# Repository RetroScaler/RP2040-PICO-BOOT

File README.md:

# RP2040-PICO-BOOT
The RP2040 PICO BOOT allows you to build your own IPL replacement modchip，It is a modified version of the Raspberry Pi Pico.

## Features

- Includes all the functions of Raspberry Pi Pico
- Without any driver, you can burn the program through Type-C cable
- Add a 'Reset' button

## Pictures

3D Picture of PCBA

The pinout 

## 🤝 Support

Contributions, issues, and feature requests are welcome!

if you like this project, stay tuned !

You can quickly purchase the finished product with this link：[Go to AliExpress shopping platform](https://www.aliexpress.us/item/3256804731684211.html?spm=a2g0o.store_pc_allProduct.8148356.3.6d2d4653RMWMQH&pdp_npi=2%40dis%21USD%21US%20%244.60%21US%20%243.27%21%21%21%21%21%40211b88f116768734920522999e0baf%2112000031082566413%21sh&gatewayAdapt=glo2usa&_randl_shipto=US)

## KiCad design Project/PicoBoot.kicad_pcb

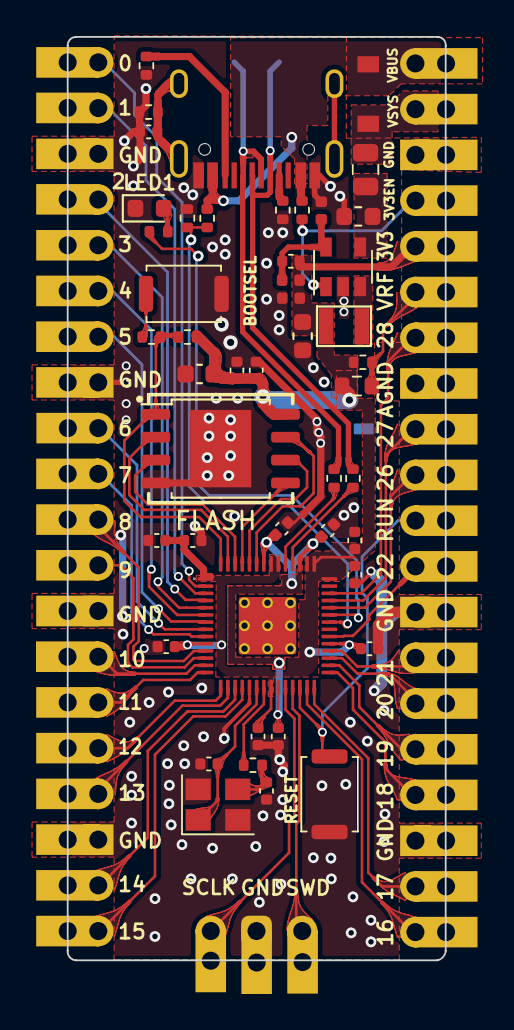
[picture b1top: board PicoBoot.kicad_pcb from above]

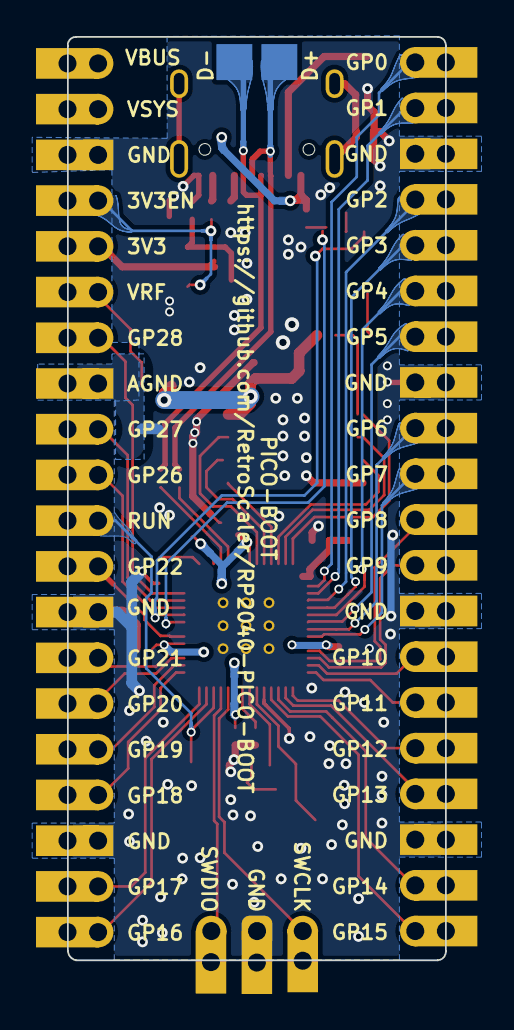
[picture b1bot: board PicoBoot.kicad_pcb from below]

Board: 2 copper layers, 21.0 x 51.3 mm, 53 parts (5 on the bottom side), 60 nets.

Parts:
C1, C9, C17: 10uf; C_0603_1608Metric
C2, C19: 22pf; C_0402_1005Metric
C3, C10: 1uf; C_0402_1005Metric
C4: 22pF; C_0402_1005Metric
C5, C6, C7, C8, C11, C12, C13, C14, C15, C16, C18: 100nf; C_0402_1005Metric
C101: 0.1uf; C_0402_1005Metric
D1: 1N4002W; D_SOD-123
F1: 0805L050WR; Fuse_0805_2012Metric
FLASH: W25Q16JVUXIQ; SOIC-8_5.23x5.23mm_P1.27mm
GPIO25_RESISTOR1: 470; R_0402_1005Metric
J2: TSA343G00-250J2; SW_Push_SPST_NO_Alps_SKRK
J3, J4: 2.54mm header 01x20; PinHeader_1x20_P2.54mm_Vertical
J5: Conn_01x03_Male; PinHeader_1x03_P2.54mm_Vertical
L1: 2.2uH; WPN252010UF2R2MT
LED1: LED_0603; LED_0603_1608Metric
NT1: NetTie_2; NetTie-2_SMD_Pad0.5mm
R1, R11: 1K; R_0402_1005Metric
R2, R103: 10K; R_0402_1005Metric
R3, R4: 27r; R_0402_1005Metric
R5, R6: 5.1K; R_0402_1005Metric
R7: 100K; R_0402_1005Metric
R8: 680K; R_0402_1005Metric
R9: 200; R_0603_1608Metric
R10: 1; R_0402_1005Metric
R12: 150K; R_0402_1005Metric
R101: 5.6K; R_0402_1005Metric
R102: 220; R_0402_1005Metric
RSW1: TSA343G00-250J2; SW_Push_SPST_NO_Alps_SKRK
TP1, TP2: TestPoint; CustomTestPoint
U1: TD6810-ADJ; SOT-23-5
U3: RP2040; RP2040-QFN-56
USB1: TYPE-C-31-M-12; HRO-TYPE-C-31-M-12
Y1: 3225_4P; Crystal_SMD_3225-4Pin_3.2x2.5mm

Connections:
3V3_EN: J4.4, R7.1, U1.1 (RUN)
+1V1: C3.1, C6.1, C7.1, U3.23 (DVDD), U3.45 (VREG_VOUT), U3.50 (DVDD)
+3V3: C4.2, C5.1, C8.1, C9.1, C10.1, C11.1, C12.1, C13.1, C14.1, C15.1, C16.1, C17.1, C18.1, FLASH.8 (VCC), J4.5, L1.2, R2.1, R8.1, R9.1, R10.2, U3.1 (IOVDD), U3.10 (IOVDD), U3.22 (IOVDD), U3.33 (IOVDD), U3.42 (IOVDD), U3.43 (ADC_AVDD), U3.44 (VREG_IN), U3.48 (USB_VDD), U3.49 (IOVDD)
/ADC_VREF: J4.6, R9.2, R10.1
/D+: R3.2, U3.47 (USB_DP)
/D-: R4.2, U3.46 (USB_DM)
/GPIO0: J3.20, U3.2 (GPIO0)
/GPIO1: J3.19, U3.3 (GPIO1)
/GPIO2: J3.17, U3.4 (GPIO2)
/GPIO3: J3.16, U3.5 (GPIO3)
/GPIO4: J3.15, U3.6 (GPIO4)
/GPIO5: J3.14, U3.7 (GPIO5)
/GPIO6: J3.12, U3.8 (GPIO6)
/GPIO7: J3.11, U3.9 (GPIO7)
/GPIO8: J3.10, U3.11 (GPIO8)
/GPIO9: J3.9, U3.12 (GPIO9)
/GPIO10: J3.7, U3.13 (GPIO10)
/GPIO11: J3.6, U3.14 (GPIO11)
/GPIO12: J3.5, U3.15 (GPIO12)
/GPIO13: J3.4, U3.16 (GPIO13)
/GPIO14: J3.2, U3.17 (GPIO14)
/GPIO15: J3.1, U3.18 (GPIO15)
/GPIO16: J4.20, U3.27 (GPIO16)
/GPIO17: J4.19, U3.28 (GPIO17)
/GPIO18: J4.17, U3.29 (GPIO18)
/GPIO19: J4.16, U3.30 (GPIO19)
/GPIO20: J4.15, U3.31 (GPIO20)
/GPIO21: J4.14, U3.32 (GPIO21)
/GPIO22: J4.12, U3.34 (GPIO22)
/GPIO24: R101.2, R103.1, U3.36 (GPIO24)
/GPIO25: GPIO25_RESISTOR1.2, U3.37 (GPIO25)
/GPIO26_ADC0: J4.10, U3.38 (GPIO26_ADC0)
/GPIO27_ADC1: J4.9, U3.39 (GPIO27_ADC1)
/GPIO28_ADC2: J4.7, U3.40 (GPIO28_ADC2)
/QSPI_SCLK: FLASH.6 (CLK), U3.52 (QSPI_SCLK)
/QSPI_SD0: FLASH.5 (DI(IO0)), U3.53 (QSPI_SD0)
/QSPI_SD1: FLASH.2 (DO(IO1)), U3.55 (QSPI_SD1)
/QSPI_SD2: FLASH.3 (IO2), U3.54 (QSPI_SD2)
/QSPI_SD3: FLASH.7 (IO3), U3.51 (QSPI_SD3)
/QSPI_SS: FLASH.1 (~CS), R1.1, R2.2, U3.56 (QSPI_SS)
/RUN: J4.11, RSW1.2, U3.26 (RUN)
/SWCLK: J5.1, U3.24 (SWCLK)
/SWD: J5.3, U3.25 (SWD)
/~USB_BOOT: J2.1, R1.2
AGND: J4.8, NT1.2
GND: C1.2, C2.1, C3.2, C5.2, C6.2, C7.2, C8.2, C9.2, C10.2, C11.2, C12.2, C13.2, C14.2, C15.2, C16.2, C17.2, C18.2, C19.1, C101.1, FLASH.4 (GND), J2.2, J3.3, J3.8, J3.13, J3.18, J4.3, J4.13, J4.18, J5.2, LED1.1 (K), NT1.1, R5.1, R6.1, R12.1, R102.2, R103.2, RSW1.1, U1.2 (GND), U3.19 (TESTEN), U3.57 (GND), USB1.1 (GND), USB1.12 (GND), Y1.2, Y1.4
unnamed: C1.1, F1.1, U1.4 (VIN)
unnamed: C4.1, R8.2, R12.2, U1.5 (FB)
unnamed: C19.2, R11.2, Y1.3
unnamed: C101.2, R102.1, USB1.13 (SHIELD)
unnamed: GPIO25_RESISTOR1.1, LED1.2 (A)
unnamed: L1.1, U1.3 (SW)
unnamed: R5.2, USB1.4 (CC1)
unnamed: R6.2, USB1.10 (CC2)
USB_D+: R3.1, TP1.1, USB1.6 (DP1), USB1.8 (DP2)
USB_D-: R4.1, TP2.1, USB1.5 (DN2), USB1.7 (DN1)
VBUS: D1.2 (A), J4.1, R7.2, R101.1, USB1.2 (VBUS), USB1.11 (VBUS)
VSYS: D1.1 (K), F1.2, J4.2
XIN: C2.2, U3.20 (XIN), Y1.1
XOUT: R11.1, U3.21 (XOUT)

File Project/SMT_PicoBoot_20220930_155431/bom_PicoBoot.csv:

Comment,Description,Designator,Footprint,LibRef,Pins,Quantity
"","",",,","","","",3
"10uf 0603","Capacitor SMD 0603 (1608 Metric), square (rectangular) end terminal, IPC_7351 nominal, (Body size source: http://www.tortai-tech.com/upload/download/20111020232333690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, generated with kicad-footprint-generator","C1,C9","C_0603_1608Metric","","",2
"22pf 0402","Capacitor SMD 0402 (1005 Metric), square (rectangular) end terminal, IPC_7351 nominal, (Body size source: IPC-SM-782 page 76, https://www.pcb-3d.com/wordpress/wp-content/uploads/ipc-sm-7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, generated with kicad-footprint-generator","C2,C19","C_0402_1005Metric","","",2
"1uf 0402","Capacitor SMD 0402 (1005 Metric), square (rectangular) end terminal, IPC_7351 nominal, (Body size source: IPC-SM-782 page 76, https://www.pcb-3d.com/wordpress/wp-content/uploads/ipc-sm-7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, generated with kicad-footprint-generator","C3,C10","C_0402_1005Metric","","",2
"22pF ","Capacitor SMD 0402 (1005 Metric), square (rectangular) end terminal, IPC_7351 nominal, (Body size source: IPC-SM-782 page 76, https://www.pcb-3d.com/wordpress/wp-content/uploads/ipc-sm-7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, generated with kicad-footprint-generator","C4","C_0402_1005Metric","","",1
"100nf 0402","Capacitor SMD 0402 (1005 Metric), square (rectangular) end terminal, IPC_7351 nominal, (Body size source: IPC-SM-782 page 76, https://www.pcb-3d.com/wordpress/wp-content/uploads/ipc-sm-7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, generated with kicad-footprint-generator","C6,C7,C11,C13,C14,C8,C5,C16,C18,C15,C12","C_0402_1005Metric","","",11
"10uf 0402","Capacitor SMD 0603 (1608 Metric), square (rectangular) end terminal, IPC_7351 nominal, (Body size source: IPC-SM-782 page 76, https://www.pcb-3d.com/wordpress/wp-content/uploads/ipc-sm-7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, generated with kicad-footprint-generator","C17","C_0603_1608Metric","","",1
"0.1uf 0402","Capacitor SMD 0402 (1005 Metric), square (rectangular) end terminal, IPC_7351 nominal, (Body size source: IPC-SM-782 page 76, https://www.pcb-3d.com/wordpress/wp-content/uploads/ipc-sm-7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, generated with kicad-footprint-generator","C101","C_0402_1005Metric","","",1
"1N4002W","SOD-123","D1","D_SOD-123","","",1
"0805L050WR","Fuse SMD 0805 (2012 Metric), square (rectangular) end terminal, IPC_7351 nominal, (Body size source: https://docs.google.com/spreadsheets/d/1BsfQQcO9C6DZCsRaXUlF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, generated with kicad-footprint-generator","F1","Fuse_0805_2012Metric","","",1
"W25Q16JVUXIQ","SOIC, 8 Pin (http://www.winbond.com/resource-files/w25q32jv%20revg%200327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, generated with kicad-footprint-generator ipc_gullwing_generator.py","FLASH","SOIC-8_5.23x5.23mm_P1.27mm","","",1
"LED_0402","LED SMD 0402 (1005 Metric), square (rectangular) end terminal, IPC_7351 nominal, (Body size source: http://www.tortai-tech.com/upload/download/20111020232333690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, generated with kicad-footprint-generator","GPIO25_LED1","LED_0402_1005Metric","","",1
"470 0402","Resistor SMD 0402 (1005 Metric), square (rectangular) end terminal, IPC_7351 nominal, (Body size source: IPC-SM-782 page 72, https://www.pcb-3d.com/wordpress/wp-content/uploads/ipc-sm-7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, generated with kicad-footprint-generator","GPIO25_RESISTOR1","R_0402_1005Metric","","",1
"MountingHole","Mounting Hole 2.1mm, no annular","H4,H3,H1,H2","MountingHole_2.1mm","","",4
"TSA343G00-250J2","http://www.alps.com/prod/info/E/HTML/Tact/SurfaceMount/SKRK/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","J2,RSW1","SW_Push_SPST_NO_Alps_SKRK","","",2
"2.54mm header 01x20","Through hole straight pin header, 1x20, 2.54mm pitch, single row","J4,J3","PinHeader_1x20_P2.54mm_Vertical","","",2
"Conn_01x03_Male","Through hole straight pin header, 1x03, 2.54mm pitch, single row","J5","PinHeader_1x03_P2.54mm_Vertical","","",1
"2.2uH","","L1","WPN252010UF2R2MT","","",1
"NetTie_2","Net tie, 2 pin, 0.5mm square SMD pads","NT1","NetTie-2_SMD_Pad0.5mm","","",1
"1K 0402","Resistor SMD 0402 (1005 Metric), square (rectangular) end terminal, IPC_7351 nominal, (Body size source: IPC-SM-782 page 72, https://www.pcb-3d.com/wordpress/wp-content/uploads/ipc-sm-7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, generated with kicad-footprint-generator","R1,R11","R_0402_1005Metric","","",2
"10K 0402","Resistor SMD 0402 (1005 Metric), square (rectangular) end terminal, IPC_7351 nominal, (Body size source: IPC-SM-782 page 72, https://www.pcb-3d.com/wordpress/wp-content/uploads/ipc-sm-7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, generated with kicad-footprint-generator","R2,R103","R_0402_1005Metric","","",2
"27r 0402 resistor","Resistor SMD 0402 (1005 Metric), square (rectangular) end terminal, IPC_7351 nominal, (Body size source: IPC-SM-782 page 72, https://www.pcb-3d.com/wordpress/wp-content/uploads/ipc-sm-7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, generated with kicad-footprint-generator","R4,R3","R_0402_1005Metric","","",2
"5.1K 0402","Resistor SMD 0402 (1005 Metric), square (rectangular) end terminal, IPC_7351 nominal, (Body size source: IPC-SM-782 page 72, https://www.pcb-3d.com/wordpress/wp-content/uploads/ipc-sm-7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, generated with kicad-footprint-generator","R5,R6","R_0402_1005Metric","","",2
"100K 0402","Resistor SMD 0402 (1005 Metric), square (rectangular) end terminal, IPC_7351 nominal, (Body size source: IPC-SM-782 page 72, https://www.pcb-3d.com/wordpress/wp-content/uploads/ipc-sm-7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, generated with kicad-footprint-generator","R7","R_0402_1005Metric","","",1
"680K","Resistor SMD 0402 (1005 Metric), square (rectangular) end terminal, IPC_7351 nominal, (Body size source: http://www.tortai-tech.com/upload/download/20111020232333690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, generated with kicad-footprint-generator","R8","R_0402_1005Metric","","",1
"200 0603","Resistor SMD 0603 (1608 Metric), square (rectangular) end terminal, IPC_7351 nominal, (Body size source: IPC-SM-782 page 72, https://www.pcb-3d.com/wordpress/wp-content/uploads/ipc-sm-7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, generated with kicad-footprint-generator","R9","R_0603_1608Metric","","",1
"1 0402","Resistor SMD 0402 (1005 Metric), square (rectangular) end terminal, IPC_7351 nominal, (Body size source: IPC-SM-782 page 72, https://www.pcb-3d.com/wordpress/wp-content/uploads/ipc-sm-7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, generated with kicad-footprint-generator","R10","R_0402_1005Metric","","",1
"150K","Resistor SMD 0402 (1005 Metric), square (rectangular) end terminal, IPC_7351 nominal, (Body size source: http://www.tortai-tech.com/upload/download/20111020232333690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, generated with kicad-footprint-generator","R12","R_0402_1005Metric","","",1
"5.6K 0402","Resistor SMD 0402 (1005 Metric), square (rectangular) end terminal, IPC_7351 nominal, (Body size source: IPC-SM-782 page 72, https://www.pcb-3d.com/wordpress/wp-content/uploads/ipc-sm-7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, generated with kicad-footprint-generator","R101","R_0402_1005Metric","","",1
"220 0402","Resistor SMD 0402 (1005 Metric), square (rectangular) end terminal, IPC_7351 nominal, (Body size source: IPC-SM-782 page 72, https://www.pcb-3d.com/wordpress/wp-content/uploads/ipc-sm-7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, generated with kicad-footprint-generator","R102","R_0402_1005Metric","","",1
"SON127P800X600X80-9N","","REF**","SON127P800X600X80-9N","","",1
"TestPoint","SMD pad as test Point, diameter 1.0mm","TP1,TP2","CustomTestPoint","","",2
"TD6810-ADJ","5-pin SOT23 package","U1","SOT-23-5","","",1
"RP2040","QFN, 56 Pin (http://www.cypress.com/file/416486/download#page=40), generated with kicad-footprint-generator ipc_dfn_qfn_generator.py","U3","RP2040-QFN-56","","",1
"TYPE-C-31-M-12","","USB1","HRO-TYPE-C-31-M-12","","",1
"3225_4P","SMD Crystal SERIES SMD3225/4 http://www.txccrystal.com/images/pdf/7m-accuracy.pdf, 3.2x2.5mm^2 package","Y1","Crystal_SMD_3225-4Pin_3.2x2.5mm","","",1

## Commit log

2022-10-18 init
